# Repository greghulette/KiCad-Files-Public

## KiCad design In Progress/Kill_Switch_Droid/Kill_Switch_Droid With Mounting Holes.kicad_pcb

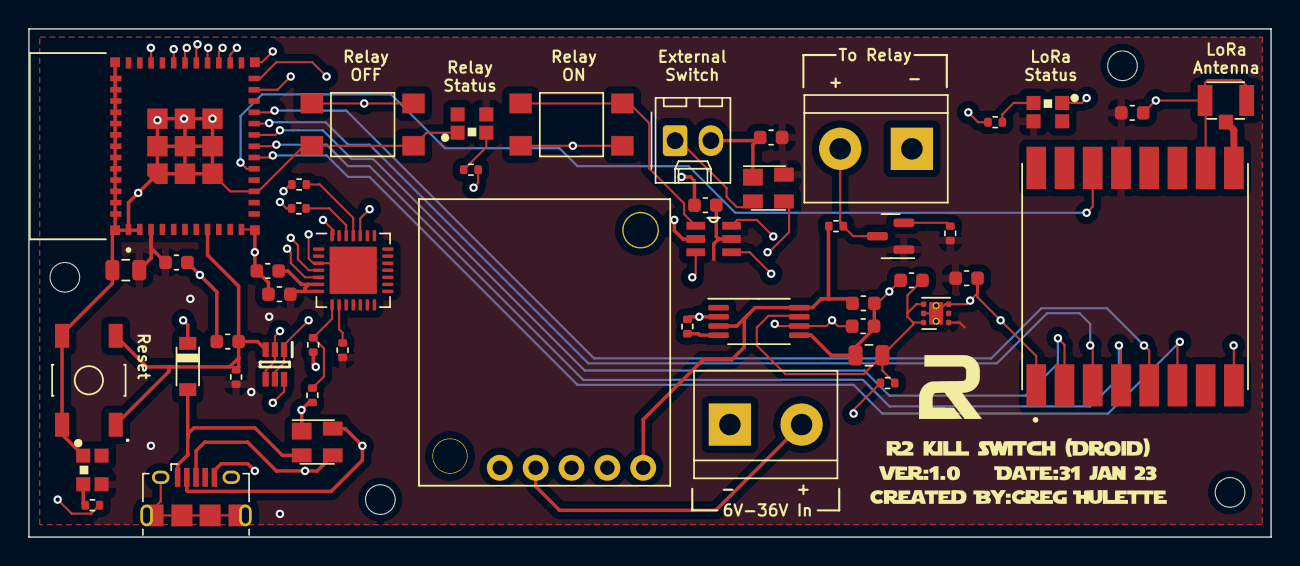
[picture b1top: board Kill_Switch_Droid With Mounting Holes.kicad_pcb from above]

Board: 4 copper layers, 88.0 x 36.0 mm, 49 parts (0 on the bottom side), 41 nets.

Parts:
C1, C8: 10uF; C_0805_2012Metric
C2, C3, C5, C9, C10, C11, C12, C13: .1uF; C_0603_1608Metric
C4: 4.7uF; C_0603_1608Metric
C6, C7: 1uF; C_0603_1608Metric
D1: B5819W-TP; SOD3716X135N
D2: SP0503BAHTG; SOT-143
J1: USB_B_Micro; USB_Micro-B_Amphenol_10118194_Horizontal
J2: Power In; TerminalBlock_bornier-2_P5.08mm
J3: U.FL-R-SMT-1(10); HRS_U.FL-R-SMT-1(10)
J4: External Switch In; Molex_KK-254_AE-6410-02A_1x02_P2.54mm_Vertical
J5: Output; TerminalBlock_bornier-2_P5.08mm
L1, L2, L3: WS2812B-2020
Q2: UMH3N; SOT65P230X110-6N
Q3: BSS138; SOT-23
R1, R7, R8: 10K; R_0402_1005Metric
R2, R3, R6: 1K; R_0402_1005Metric
R4: 22.1K; R_0402_1005Metric
R5: 47.5K; R_0402_1005Metric
R9, R10: 400; R_0402_1005Metric
R14, R16, R17: 470; R_0402_1005Metric
S1: TL3342F160QG; SW_TL3342F160QG
S2, S3: TL3305CF260QG
U1: ESP32-PICO-MINI-02; MODULE_ESP32-PICO-MINI-02
U2: CP2102N-A02-GQFN28; QFN-28-1EP_5x5mm_P0.5mm_EP3.35x3.35mm
U3: LP5912-3.3DRV; WSON-6-1EP_2x2mm_P0.65mm_EP1x1.6mm_ThermalVias
U4: TPS2115APW; TSSOP-8_4.4x3mm_P0.65mm
U5: RFM95W-915S2
U6: MAX6817EUT+T; SOT95P280X145-6N
U7: D24V550F5_Step_Down_Regulator; VoltageREG_2851
U8: MAX6816; SOT-143

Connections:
+3V3: C1.1, C2.1, C4.1, C5.1, C7.2, C10.1, C11.2, C13.2, L1.4 (VDD), L2.4 (VDD), L3.4 (VDD), Q3.1 (G), R1.1, R6.2, R7.1, U1.3 (3V3), U2.6 (VDD), U2.7 (VREGIN), U3.1 (OUT), U5.13 (3.3V), U6.5 (VCC), U8.4 (VCC)
+5V: C9.1, R8.1, U4.3 (D1), U4.8 (IN1), U7.5 (VOut)
DI0_LORA: U1.16 (IO26), U5.14 (DIO0)
DTR: Q2.1 (E1), Q2.5 (B2), U2.28 (DTR)
EXT_SW_OUT: U1.24 (IO4), U8.3 (OUT)
GND: C1.2, C2.2, C3.2, C4.2, C5.2, C6.1, C7.1, C8.1, C9.2, C10.2, C11.1, C12.2, C13.1, D2.1 (A), J1.5 (GND), J2.1, J3.1, J3.3, J4.2, J5.1, L1.2 (GND), L2.2 (GND), L3.2 (GND), R5.2, R9.2, R10.2, S1.3, S1.4, S2.3, S2.4, S3.3, S3.4, U1.1 (GND), U1.2 (GND), U1.11 (GND), U1.14 (GND), U1.36 (GND), U1.37 (GND), U1.38 (GND), U1.39 (GND), U1.40 (GND), U1.41 (GND), U1.42 (GND), U1.43 (GND), U1.44 (GND), U1.45 (GND), U1.46 (GND), U1.47 (GND), U1.48 (GND), U1.49 (GND), U1.50 (GND), U1.51 (GND), U1.52 (GND), U1.53 (GND), U1.54 (GND), U1.55 (GND), U1.56 (GND), U1.57 (GND), U1.58 (GND), U1.59 (GND), U1.60 (GND), U1.61 (GND), U2.3 (GND), U2.29 (GND), U3.3 (PG), U3.5 (GND), U3.7 (EP), U4.2 (D0), U4.5 (GND), U5.1 (GND), U5.8 (GND), U5.10 (GND), U6.2 (GND), U7.2 (GND), U7.4 (GND), U8.1 (GND)
GPIO0: Q2.6 (C1), U1.23 (IO0)
LORA_LED_DATA: R14.2, U1.26 (IO20)
MISO_LORA: U1.19 (IO12), U5.2 (MISO)
MOSI_LORA: U1.20 (IO13), U5.3 (MOSI)
NSS_LORA: U1.21 (IO15), U5.5 (NSS)
unnamed: C6.2, C8.2, R10.1, U3.4 (EN), U3.6 (IN), U4.7 (OUT)
unnamed: D1.A, D2.2 (K), J1.1 (VBUS)
unnamed: J3.2, U5.9 (ANT)
unnamed: J4.1, U8.2 (IN)
unnamed: J5.2, Q3.3 (D), R8.2
unnamed: L1.3 (DI), R14.1
unnamed: L2.3 (DI), R16.1
unnamed: L3.3 (DI), R17.1
unnamed: R2.1, U2.26 (TXD)
unnamed: R3.1, U2.25 (RXD)
unnamed: R4.2, R5.1, U2.8 (VBUS)
unnamed: R6.1, U2.9 (RSTb)
unnamed: R9.1, U4.4 (ILIM)
unnamed: S2.1, S2.2, U6.1 (IN1)
unnamed: S3.1, S3.2, U6.3 (IN2)
OFF_SW_OUT: U1.27 (IO7), U6.4 (OUT2)
ON_SW_OUT: U1.28 (IO8), U6.6 (OUT1)
RELAY_CONTROL: Q3.2 (S), R7.2
RELAY_LED_DATA: R17.2, U1.29 (IO5)
RESET: C3.1, Q2.3 (C2), R1.2, S1.1, S1.2, U1.8 (EN)
RESET_LORA: U1.17 (IO27), U5.6 (RESET)
RTS: Q2.2 (B1), Q2.4 (E2), U2.24 (RTS)
RXD0: R2.2, U1.30 (RXD0)
SCK_LORA: U1.18 (IO14), U5.4 (SCK)
STATUS_LED_DATA: R16.2, U1.33 (IO19)
TXD0: R3.2, U1.31 (TXD0)
USB_DN: D2.4 (K), J1.2 (D-), U2.5 (D-)
USB_DP: D2.3 (K), J1.3 (D+), U2.4 (D+)
VBUS: C12.1, D1.C, R4.1, U4.6 (IN2)
VIN: J2.2, U7.1 (VIN)

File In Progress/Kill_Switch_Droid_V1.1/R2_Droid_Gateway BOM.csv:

Source:,,/Users/gregoryhulette/Documents/GitHub/KiCad-Files-Public/In Progress/Kill_Switch_Droid_V1.1/Kill_Switch_Droid.kicad_sch,,,,,,,,,,,,,,,,,,,,,,,,,,,,,,,,
Date:,,"Thursday, July 06, 2023 at 09:08:25 AM",,,,,,,,,,,,,,,,,,,,,,,,,,,,,,,,
Tool:,,Eeschema (6.0.0-0),,,,,,,,,,,,,,,,,,,,,,,,,,,,,,,,
Generator:,,/Applications/KiCad/KiCad.app/Contents/SharedSupport/plugins/bom_csv_grouped_by_value.py,,,,,,,,,,,,,,,,,,,,,,,,,,,,,,,,
Component Count:,,47,,,,,,,,,,,,,,,,,,,,,,,,,,,,,,,,
,,,,,,,,,,,,,,,,,,,,,,,,,,,,,,,,,,
Individual Components:,,,,,,,,,,,,,,,,,,,,,,,,,,,,,,,,,,
,,,,,,,,,,,,,,,,,,,,,,,,,,,,,,,,,,
Item,Designator,Qty,Manufacturers Name,Manufacturers Part Number,Description/Value,Footprint,Type,LibPart,,Datasheet,DESCRIPTION,Digikey Part Number,HEIGHT,LCSC,MANUFACTURER,MANUFACTURER_NAME,MANUFACTURER_PART_NUMBER,MAXIMUM_PACKAGE_HEIGHT,MF,MPN,Manufacturer,Manufacturer's Part Number,Manufacturers Name,Manufacturers Part Number,Mouser Part Number,OC_FARNELL,OC_MOUSER,OC_NEWARK,PACKAGE,PARTREV,PRICE_SAMPLE,STANDARD,SUPPLIER,TECHNOLOGY
1,"C1, C8",2,Würth Elektronik,CS2012X7R106K100NRE,10uF,Capacitor_SMD:C_0805_2012Metric,SMT,Device:C_Small,,https://www.we-online.com/katalog/datasheet/885012107014.pdf,,,,C1222438,,,,,,,,CS2012X7R106K100NRE,Würth Elektronik,CS2012X7R106K100NRE,,,,,,,,,,
2,"C2, C3, C5, C9, C10, C11, C12",7, Samsung Electro-Mechanics,CL05B104KB54PNC,.1uF,Capacitor_SMD:C_0402_1005Metric,SMT,Device:C_Small,,https://www.we-online.com/katalog/datasheet/885012206020.pdf,,,,C307331,,,,,,,,, Samsung Electro-Mechanics,CL05B104KB54PNC,,,,,,,,,,
3,C4,1, Murata Electronics,GCM21BR71C475KA67L,4.7uF,Capacitor_SMD:C_0805_2012Metric,SMT,Device:C_Small,,https://www.we-online.com/katalog/datasheet/885012106005.pdf,,,,C126590,,,,,,,,, Murata Electronics,GCM21BR71C475KA67L,,,,,,,,,,
4,"C6, C7",2,Murata Electronics,GRM188B31H105KAALD,1uF,Capacitor_SMD:C_0603_1608Metric,SMT,Device:C_Small,,~,,,,C913562,,,,,,,,,Murata Electronics,GRM188B31H105KAALD,,,,,,,,,,
5,D1,1,Micro Commercial Co,B5819W-TP,B5819W-TP,Custom:SOD3716X135N,SMT,Custom:B5819W-TP,,https://www.mccsemi.com/pdf/Products/B5817W-B5819W(SOD-123).pdf,,B5819W-TPMSCT-ND,,C84354,Micro Commercial Components,,,,,,,,Micro Commercial Co,B5819W-TP,833-B5819W-TP ,,,,,,,,,
6,D2,1,Littelfuse Inc.,SP0503BAHTG,SP0503BAHTG,Package_TO_SOT_SMD:SOT-143,SMT,Power_Protection:SP0503BAHT,,http://www.littelfuse.com/~/media/files/littelfuse/technical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,,F2715CT-ND,,C7074,,,,,,,,,Littelfuse Inc.,SP0503BAHTG,576-SP0503BAHTG ,,,,,,,,,
7,J1,1,Amphenol ICC (FCI),10118194-0001LF,USB_B_Micro,Connector_USB:USB_Micro-B_Amphenol_10118194_Horizontal,SMT,Connector:USB_B_Micro,,https://www.amphenol-cs.com/media/wysiwyg/files/drawing/1011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,,609-4618-1-ND,,C132563,,,,,,,,,Amphenol ICC (FCI),10118194-0001LF,649-10118194-0001LF ,,,,,,,,,
8,J2,1, Ningbo Kangnex Elec,WJ500V-5.08-2P ,Power In,TerminalBlock:TerminalBlock_bornier-2_P5.08mm,THT,Connector:Screw_Terminal_01x02,,~,,,,C8465,,,,,,,,, Ningbo Kangnex Elec,WJ500V-5.08-2P ,,,,,,,,,,
9,J3,1,MOLEX,733910083,73391-0083,Custom:73391-0083,THT,Custom:73391-0083,,,"Molex Right Angle 50 PCB Mount SMA Connector, Solder Termination",,,C493445,,,,,Molex,73391-0083,Molex,73391-0083,MOLEX,733910083,,2612349,538-73391-0083,,,,"3,08",,,THT
10,J4,1,MOLEX,22232021,External Switch In,Connector_Molex:Molex_KK-254_AE-6410-02A_1x02_P2.54mm_Vertical,THT,Connector_Generic:Conn_01x02,,~,,,,C234180,,,,,,,,,MOLEX,22232021,,,,,,,,,,
11,J5,1,Ningbo Kangnex Elec,WJ500V-5.08-2P ,Output,TerminalBlock:TerminalBlock_bornier-2_P5.08mm,THT,Connector:Screw_Terminal_01x02,,~,,,,C8465,,,,,,,,,Ningbo Kangnex Elec,WJ500V-5.08-2P ,,,,,,,,,,
12,J6,1,MOLEX,22272031,Conn_01x03,Connector_Molex:Molex_KK-254_AE-6410-03A_1x03_P2.54mm_Vertical,THT,Connector_Generic:Conn_01x03,,~,,,,C471416,,,,,,,MOLEX,,MOLEX,22272031,,,,,,,,,,
13,"L1, L2, L3",3,Worldsemi,WS2812B-2020,WS2812B-2020,Custom:WS2812B-2020,SMT,LED:WS2812B-2020,,,,,,C965555,,,,,,,,,Worldsemi,WS2812B-2020,,,,,,,,,,
14,Q2,1,ROHM Semiconductor,UMH3NTN ,UMH3N,Custom:SOT65P230X110-6N,SMT,Custom:UMH3N,,https://www.mouser.com/datasheet/2/348/umh3ntn-e-1872947.pdf,2 NPN pre-biased (Dual) 100mA 50V SC-70-6(SOT-363) Digital Transistors RoHS,UMH3NTNCT-ND,1.1mm,C123008,,Changjiang Electronics Tech (CJ),UMH3N,,,,,,ROHM Semiconductor,UMH3NTN ,755-UMH3NTN ,,,,,,,,,
15,Q3,1,Diodes Incorporated,BSS138DW-7-F,BSS138,Package_TO_SOT_SMD:SOT-23,SMT,Transistor_FET:BSS138,,https://www.onsemi.com/pub/Collateral/BSS138-D.PDF,,,,C154900,,,,,,,,,Diodes Incorporated,BSS138DW-7-F,,,,,,,,,,
16,"R1, R7, R8",3,YAGEO,RC0402JR-0710KL,10K,Resistor_SMD:R_0402_1005Metric,SMT,Device:R_Small,,https://www.yageo.com/upload/media/product/productsearch/dat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,,311-10KJRCT-ND,,C60489,,,,,,,,,YAGEO,RC0402JR-0710KL,603-RC0402JR-0710KL ,,,,,,,,,
17,"R2, R3, R6",3,YAGEO,RC0402JR-071KL,1K,Resistor_SMD:R_0402_1005Metric,SMT,Device:R_Small,,https://www.yageo.com/upload/media/product/productsearch/dat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,,311-1.0KJRCT-ND,,C105637,,,,,,,,,YAGEO,RC0402JR-071KL,603-RC0402JR-071KL ,,,,,,,,,
18,R4,1,YAGEO,RC0402JR-0722KL,22.1K,Resistor_SMD:R_0402_1005Metric,SMT,Device:R_Small,,https://www.yageo.com/upload/media/product/productsearch/dat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,,311-22KJRCT-ND,,C137898,,,,,,,,,YAGEO,RC0402JR-0722KL,603-RC0402JR-0722KL ,,,,,,,,,
19,R5,1,YAGEO,RC0402FR-0747K5L,47.5K,Resistor_SMD:R_0402_1005Metric,SMT,Device:R_Small,,https://www.yageo.com/upload/media/product/productsearch/dat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,,311-47.5KLRCT-ND,,C137974,,,,,,,,,YAGEO,RC0402FR-0747K5L,603-RC0402FR-0747K5L ,,,,,,,,,
20,"R9, R10",2,Meritek,CR204000F,400,Resistor_SMD:R_0402_1005Metric,SMT,Device:R_Small,,~,,,,C4044825,,,,,,,,,Meritek,CR204000F,,,,,,,,,,
21,"R14, R16, R17",3,YAGEO,RT0402BRD07470RL,470,Resistor_SMD:R_0402_1005Metric,SMT,Device:R_Small,,https://www.yageo.com/upload/media/product/productsearch/dat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,,,,C852799,,,,,,,,,YAGEO,RT0402BRD07470RL,,,,,,,,,,
22,S1,1,E-Switch,TL3342F160QG,TL3342F160QG,Custom:SW_TL3342F160QG,SMT,Custom:TL3342F160QG,,https://sten-eswitch-13110800-production.s3.amazonaws.com/sy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,,,,C2886898,E SWITCH,,,,,,,,E-Switch,TL3342F160QG,,,,,,,,,,
23,S2,1,E-Switch,TL3305CF260QG,TL3305CF260QG,Custom:TL3305CF260QG,SMT,Custom:TL3342F160QG,,https://sten-eswitch-13110800-production.s3.amazonaws.com/sy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,,,,C2886904,E SWITCH,,,,,,,,E-Switch,TL3305CF260QG,,,,,,,,,,
24,U1,1,Espressif Systems,ESP32-PICO-MINI-02-N8R2,ESP32-PICO-MINI-02,Custom:MODULE_ESP32-PICO-MINI-02,SMT,Custom:ESP32-PICO-MINI-02,,https://www.espressif.com/sites/default/files/documentation/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,,1965-ESP32-PICO-MINI-02-N8R2CT-ND,,C2980306,Espressif,,,2.55mm,,,,,Espressif Systems,ESP32-PICO-MINI-02-N8R2,356-ESP32PCOMN2PH3Q0,,,,,v1.0,,Manufacturer Recommendations,,
25,U2,1,Silicon Labs,CP2102N-A02-GQFN28,CP2102N-A02-GQFN28,Package_DFN_QFN:QFN-28-1EP_5x5mm_P0.5mm_EP3.35x3.35mm,SMT,Custom:CP2102N-A02-GQFN28,,,,336-5889-ND,,C1550553,,,,,,,,,Silicon Labs,CP2102N-A02-GQFN28,634-CP2102NA02GQFN28 ,,,,,,,,,
26,U3,1,Texas Instruments,LP5912Q3.3DRVTQ1,LP5912-3.3DRV,Package_SON:WSON-6-1EP_2x2mm_P0.65mm_EP1x1.6mm_ThermalVias,SMT,Regulator_Linear:LP5912-3.3DRV,,http://www.ti.com/lit/ds/symlink/lp5912.pdf,,,,C2876187,,,,,,,,,Texas Instruments,LP5912Q3.3DRVTQ1,,,,,,,,,,
27,U4,1,Texas Instruments,TPS2115APWR,TPS2115APW,Package_SO:TSSOP-8_4.4x3mm_P0.65mm,SMT,Custom:TPS2115APW,,https://www.ti.com/general/docs/suppproductinfo.tsp?distId=1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,,296-26918-5-ND,,C70287,,,,,,,,,Texas Instruments,TPS2115APWR,595-TPS2115APW ,,,,,,,,,
28,U5,1,RF Solutions,RFM95W-915S2,RFM95W-915S2,Custom:RFM95W-915S2,SMT,RF_Module:RFM95W-915S2,,https://www.hoperf.com/data/upload/portal/20181127/5bfcbea20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,,RFM95W-915S2-ND,,-----,,,,,,,,,RF Solutions,RFM95W-915S2,223-RFM95W-915S2 ,,,,,,,,,
29,U6,1,Analog Devices Inc./Maxim Integrated,MAX6817EUT+T,MAX6817EUT+T,Custom:SOT95P280X145-6N,SMT,Custom:MAX6817EUT+T,,https://www.analog.com/media/en/technical-documentation/data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,,,,C516788,,,,,,MAX6817EUT+T,,,Analog Devices Inc./Maxim Integrated,MAX6817EUT+T,,1299771,,68K9458,SOT23-6,,,,Maxim,

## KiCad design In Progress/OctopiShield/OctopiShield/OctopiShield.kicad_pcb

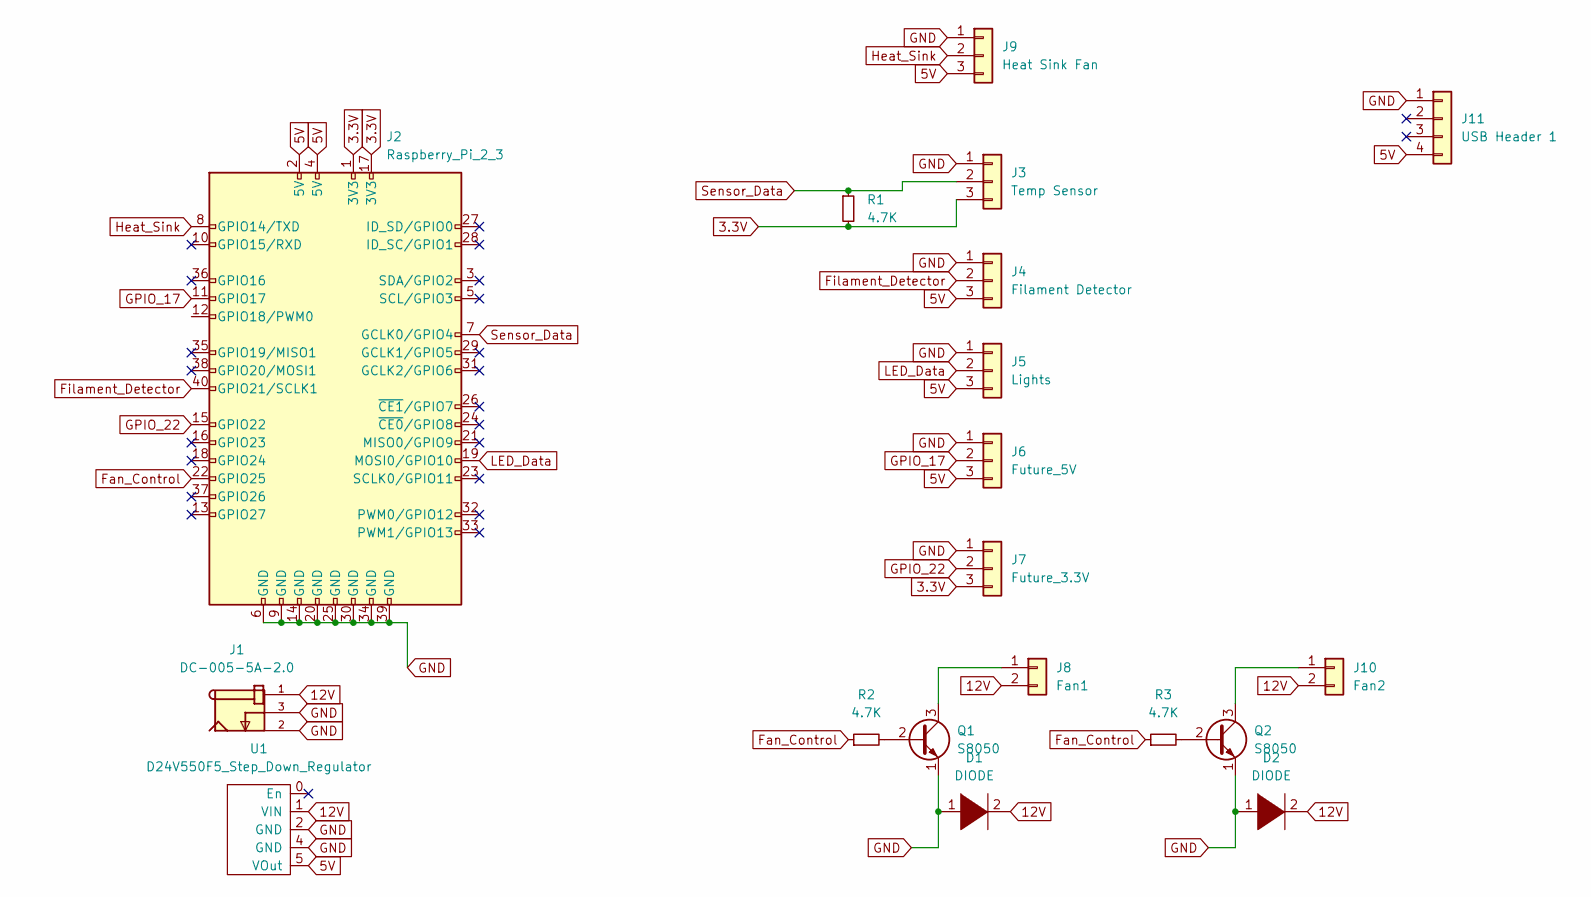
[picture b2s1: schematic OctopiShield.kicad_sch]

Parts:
D1, D2: DIODE; D_A-405_P10.16mm_Horizontal
J1: DC-005-5A-2.0; XKB_DC-005-5A-2.0; PARTREV A0
J2: Raspberry_Pi_2_3; PinSocket_2x20_P2.54mm_Vertical
J3: Temp Sensor; PinHeader_1x03_P2.54mm_Vertical
J4: Filament Detector; PinHeader_1x03_P2.54mm_Vertical
J5: Lights; PinHeader_1x03_P2.54mm_Vertical
J6: Future_5V; PinHeader_1x03_P2.54mm_Vertical
J7: Future_3.3V; PinHeader_1x03_P2.54mm_Vertical
J8: Fan1; PinHeader_1x02_P2.54mm_Vertical
J9: Heat Sink Fan; PinHeader_1x03_P2.54mm_Vertical
J10: Fan2; PinHeader_1x02_P2.54mm_Vertical
J11: USB Header 1; PinHeader_1x04_P2.54mm_Vertical
Q1, Q2: S8050; TO-92_Inline
R1, R2, R3: 4.7K; R_Axial_DIN0207_L6.3mm_D2.5mm_P10.16mm_Horizontal
U1: D24V550F5_Step_Down_Regulator; VoltageREG_2851

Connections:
3.3V: J2.1 (3V3), J2.17 (3V3), J3.3, J7.3, R1.2
5V: J2.2 (5V), J2.4 (5V), J4.3, J5.3, J6.3, J9.3, J11.4, U1.5 (VOut)
12V: D1.2 (A), D2.2 (A), J1.1, J8.2, J10.2, U1.1 (VIN)
Fan_Control: J2.22 (GPIO25), R2.1, R3.1
Filament_Detector: J2.40 (GPIO21/SCLK1), J4.2
GND: D1.1 (K), D2.1 (K), J1.2, J1.3, J2.6 (GND), J2.9 (GND), J2.14 (GND), J2.20 (GND), J2.25 (GND), J2.30 (GND), J2.34 (GND), J2.39 (GND), J3.1, J4.1, J5.1, J6.1, J7.1, J9.1, J11.1, Q1.1 (E), Q2.1 (E), U1.2 (GND), U1.4 (GND)
GPIO_17: J2.11 (GPIO17), J6.2
GPIO_22: J2.15 (GPIO22), J7.2
Heat_Sink: J2.8 (GPIO14/TXD), J9.2
LED_Data: J2.19 (MOSI0/GPIO10), J5.2
unnamed: J8.1, Q1.3 (C)
unnamed: J10.1, Q2.3 (C)
unnamed: Q1.2 (B), R2.2
unnamed: Q2.2 (B), R3.2
Sensor_Data: J2.7 (GCLK0/GPIO4), J3.2, R1.1

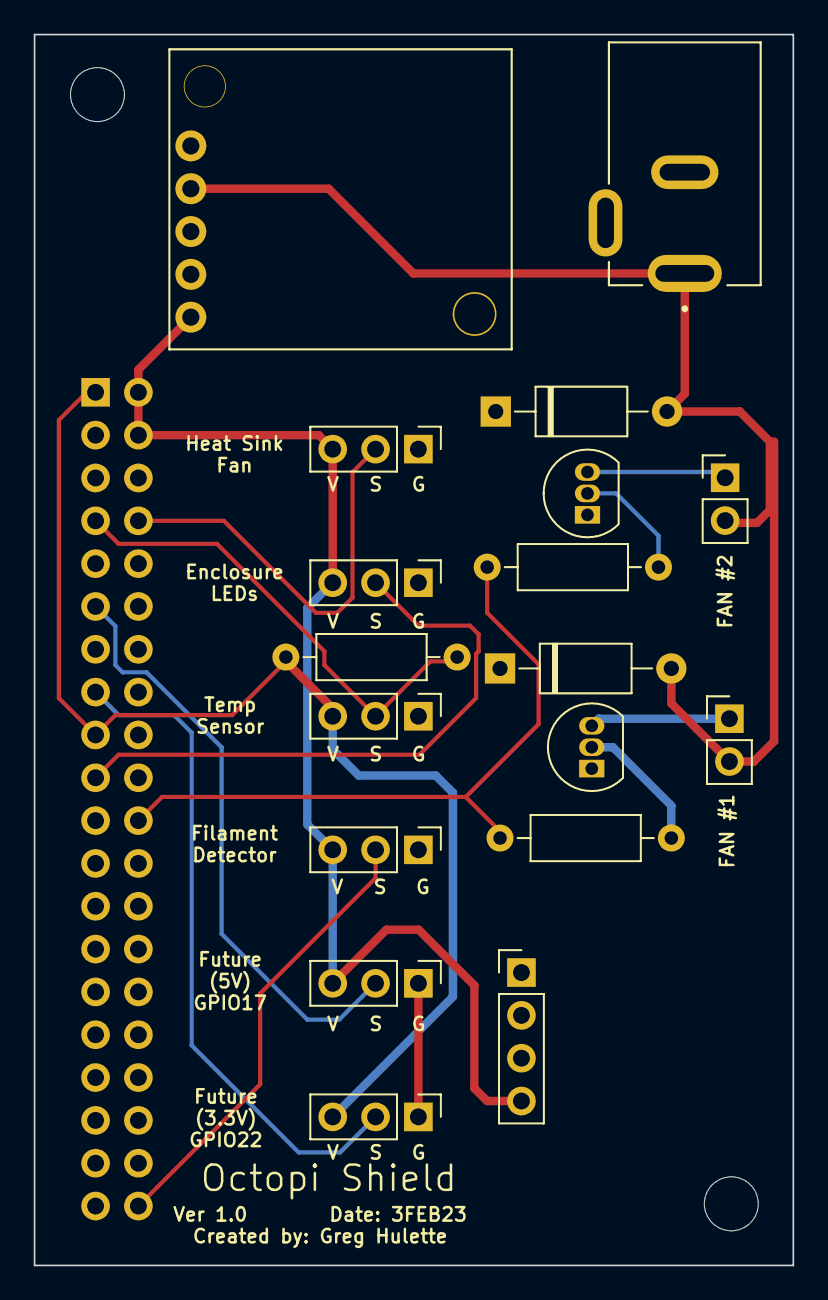
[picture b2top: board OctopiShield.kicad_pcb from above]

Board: 2 copper layers, 45.0 x 73.0 mm, 19 parts (1 on the bottom side), 15 nets.
